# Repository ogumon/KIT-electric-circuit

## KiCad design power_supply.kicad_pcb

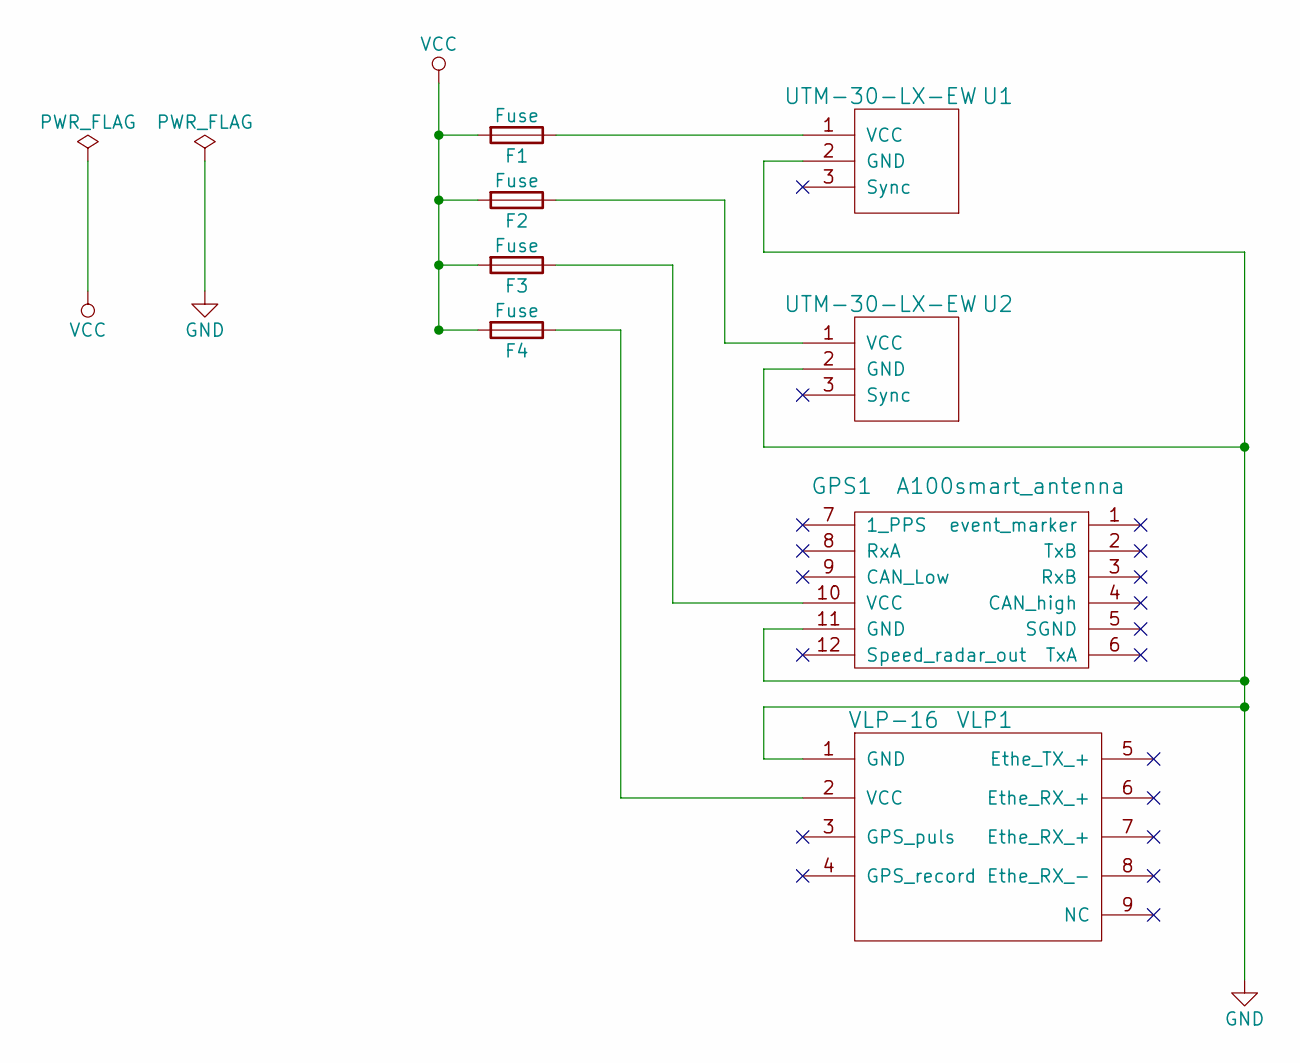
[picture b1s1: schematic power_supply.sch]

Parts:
F1, F2, F3, F4: Fuse; Fuse_holder_new
GPS1: A100smart_antenna; bridge_ELP2V_GPS
U1, U2: UTM-30-LX-EW; bridge_ELP2V
VLP1: VLP-16; bridge_ELP2V_VLP

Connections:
GND: GPS1.11 (GND), U1.2 (GND), U2.2 (GND), VLP1.1 (GND)
unnamed: F1.1, U1.1 (VCC)
unnamed: F2.1, U2.1 (VCC)
unnamed: F3.1, GPS1.10 (VCC)
unnamed: F4.1, VLP1.2 (VCC)
VCC: F1.2, F2.2, F3.2, F4.2

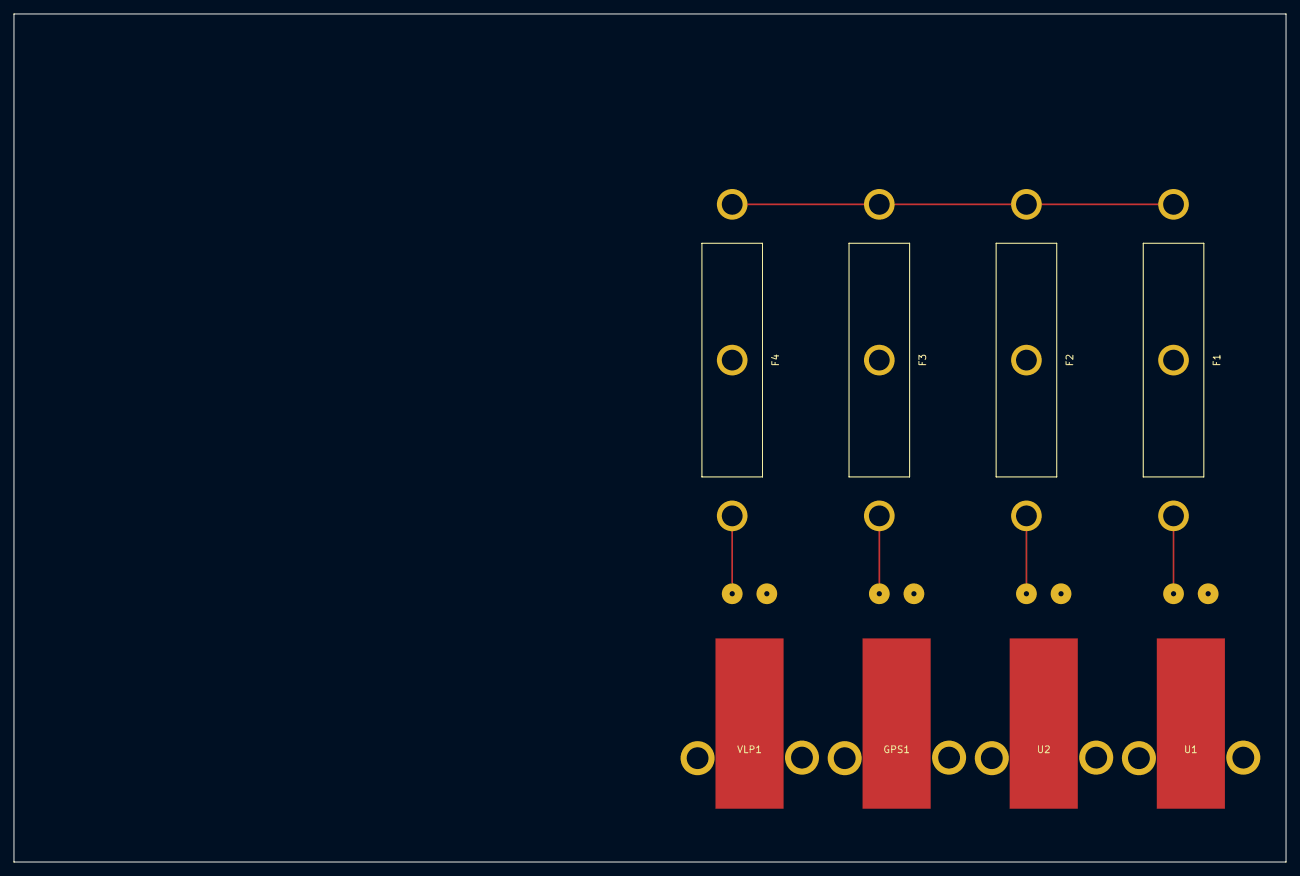
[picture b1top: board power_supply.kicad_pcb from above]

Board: 2 copper layers, 186.7 x 124.5 mm, 8 parts (0 on the bottom side), 6 nets.

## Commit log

2018-07-19 initial commit
    回路図（１回目）と、ヒューズホルダーのフットプリントを作ったあたり。
2018-08-07 Add files via upload
    cable fuse
2018-08-07 Cleaned untracked files
